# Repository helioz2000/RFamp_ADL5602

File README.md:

# RF Amplifier ADL5602
RF Amplifier based on Analog Devices ADL5602
with optional LDO power supply.

**Specification**
- 50MHz-4GHz
- 20dB Gain
- 5VDC direct supply
- Alternative 1.6V to 6V power supply

[ADL5602 Data Sheet](DataSheets/adl5602.pdf)

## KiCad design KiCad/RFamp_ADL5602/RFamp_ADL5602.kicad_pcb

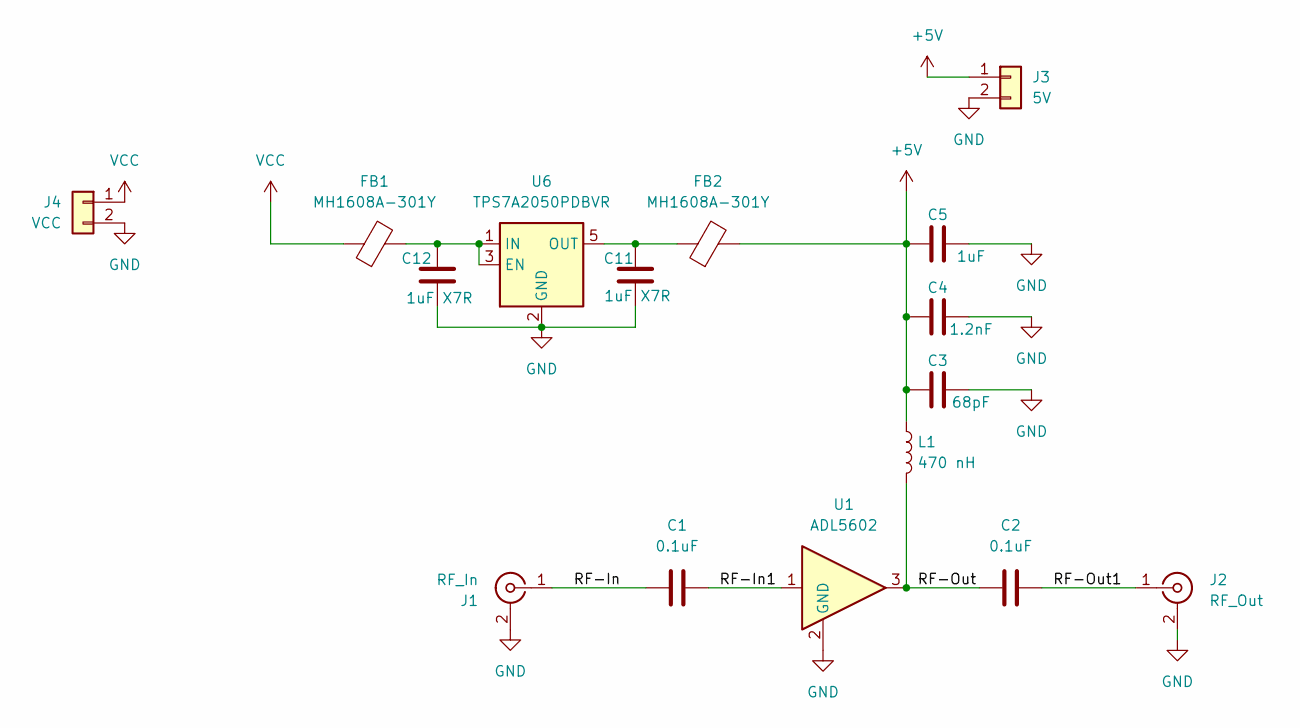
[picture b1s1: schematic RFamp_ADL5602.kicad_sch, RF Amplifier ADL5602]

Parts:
C1, C2: 0.1uF; C_0402_1005Metric
C3: 68pF; C_1206_3216Metric
C4: 1.2nF; C_1206_3216Metric
C5: 1uF; C_1206_3216Metric
C11, C12: 1uF X7R; C_0805_2012Metric_Pad1.18x1.45mm_HandSolder
FB1, FB2: MH1608A-301Y; L_0603_1608Metric_Pad1.05x0.95mm_HandSolder
J1: RF_In; SMA_Amphenol_132289_EdgeMount
J2: RF_Out; SMA_Amphenol_132289_EdgeMount
J3: 5V; PinSocket_1x02_P2.54mm_Vertical
J4: VCC; PinSocket_1x02_P2.54mm_Vertical
L1: 470 nH; L_0603_1608Metric_Pad1.05x0.95mm_HandSolder
U1: ADL5602; SOT-89-3
U6: TPS7A2050PDBVR; SOT-23-5

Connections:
+5V: C3.1, C4.1, C5.1, FB2.2, J3.1, L1.1
/RF-In: C1.1, J1.1 (In)
/RF-In1: C1.2, U1.1
/RF-Out: C2.1, L1.2, U1.3
/RF-Out1: C2.2, J2.1 (In)
GND: C3.2, C4.2, C5.2, C11.2, C12.2, J1.2 (Ext), J2.2 (Ext), J3.2, J4.2, U1.2 (GND_2), U6.2 (GND)
unnamed: C12.1, FB1.2, U6.1 (IN), U6.3 (EN)
unnamed: C11.1, FB2.1, U6.5 (OUT)
VCC: FB1.1, J4.1

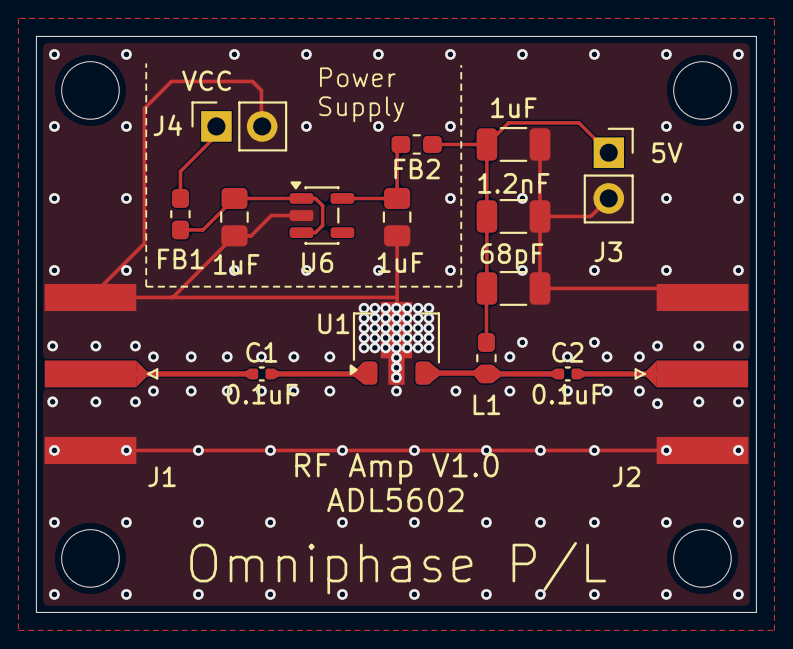
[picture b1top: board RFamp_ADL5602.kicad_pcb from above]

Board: 4 copper layers, 40.0 x 32.0 mm, 16 parts (0 on the bottom side), 9 nets.
